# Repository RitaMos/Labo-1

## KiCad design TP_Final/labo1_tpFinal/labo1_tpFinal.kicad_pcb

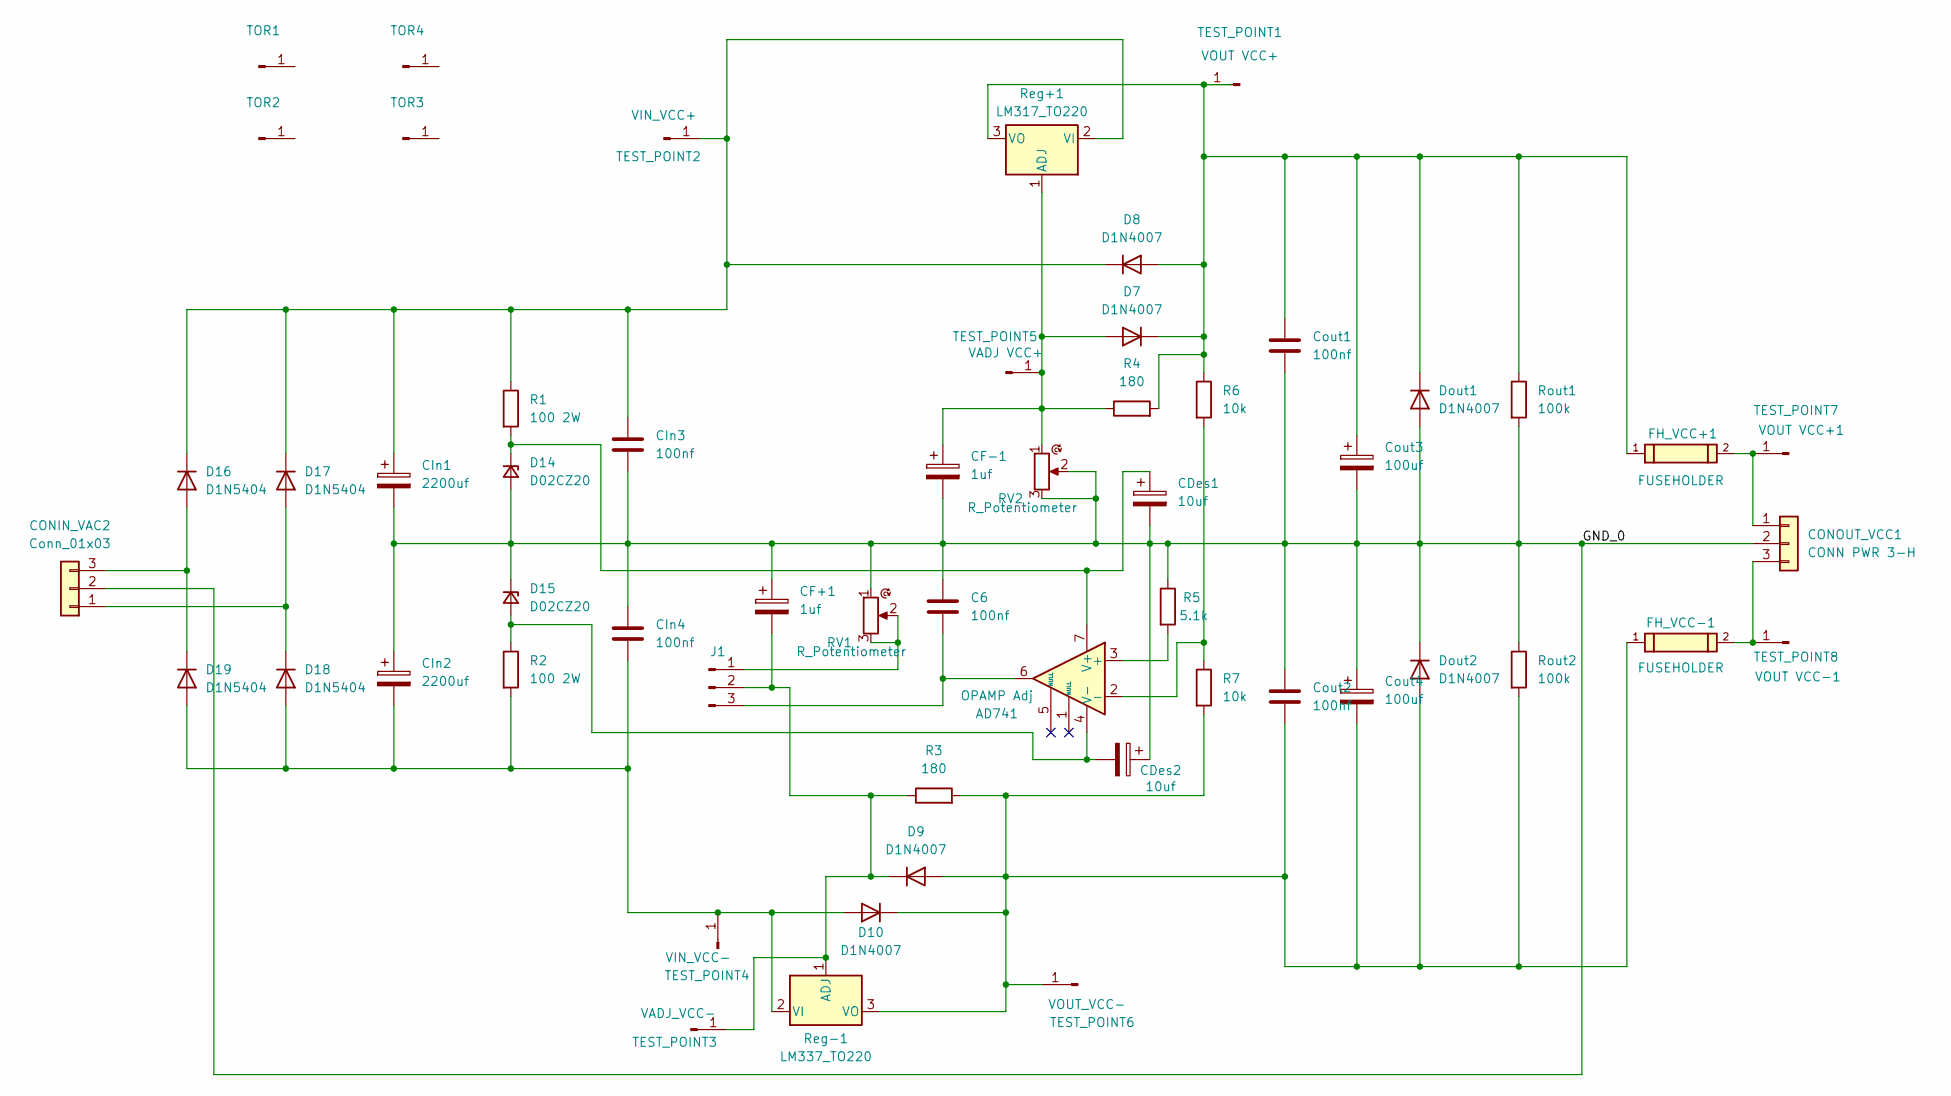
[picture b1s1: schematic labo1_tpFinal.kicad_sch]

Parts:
AD741: OPAMP Adj; N_8_ADI; MPN LM741
C6: 100nf; CAPC2012X140N; MPN C0805Y104K1RACTU
CDes1, CDes2: 10uf; CAPC2012X140N; MPN TLCR106M020RTA
CF+1: 1uf; TACR_AVX; MPN TACR105M025XTA
CF-1: 1uf; TACR_AVX; MPN TACR105M025XTA
CIn1, CIn2: 2200uf; CP_EIA-7260-15_AVX-R; MPN F750G228KRC
CIn3, CIn4: 100nf; CAPC2012X140N; MPN C0805Y104K1RACTU
CONIN_VAC2: Conn_01x03; CONN_A-6373-03A_MOL; MPN 0022232031
CONOUT_VCC1: CONN PWR 3-H; CONN_A-6373-03A_MOL; MPN 0022232031
Cout1, Cout2: 100nf; CAPC2012X140N; MPN C0805Y104K1RACTU
Cout3, Cout4: 100uf; CAPMP7.6X6_3.8N_KEM; MPN T491E107K020AT
D7, D8, D9, D10: D1N4007; P1_DO-41; MPN 1N4007
D14, D15: D02CZ20; SC-59_TOS; MPN 02CZ2.0-X
D16, D17, D18, D19: D1N5404; D_DO-201AD_P15.24mm_Horizontal; MPN 1N5404
Dout1, Dout2: D1N4007; P1_DO-41; MPN 1N4007
FH_VCC+1: FUSEHOLDER; FUSE_01110501Z; MPN 696108003002
FH_VCC-1: FUSEHOLDER; FUSE_01110501Z; MPN 696108003002
J1: Conn_01x03_Pin; WURTH_61300311121; MPN 61300311121
R1, R2: 100 2W; RES_MMP200_YAG-M; MPN MMP200JR-100R
R3, R4: 180; RESC2012X60N; MPN RNCP0805FTD180R
R5: 5.1k; RESC2012X60N; MPN RC0805JR-075K1L
R6, R7: 10k; STA_RMCF0805_STP; MPN RMCF0805FT10K0
RV1, RV2: R_Potentiometer; POT_3296W; MPN 3296W-1-202LF
Reg+1: LM317_TO220; TO254P467X1016X1971-3P; MPN LM317
Reg-1: LM337_TO220; TO-220-3_Vertical; MPN LM337T/NOPB
Rout1, Rout2: 100k; RESC2012X60N; MPN 8-2176765-8
TEST_POINT1: VOUT VCC+; TestPoint_Loop_D2.50mm_Drill1.0mm
TEST_POINT2: VIN_VCC+; TestPoint_Loop_D2.50mm_Drill1.0mm
TEST_POINT3: VADJ_VCC-; TestPoint_Loop_D2.50mm_Drill1.0mm
TEST_POINT4: VIN_VCC-; TestPoint_Loop_D2.50mm_Drill1.0mm
TEST_POINT5: VADJ VCC+; TestPoint_Loop_D2.50mm_Drill1.0mm
TEST_POINT6: VOUT_VCC-; TestPoint_Loop_D2.50mm_Drill1.0mm
TEST_POINT7: VOUT VCC+1; TestPoint_Loop_D2.50mm_Drill1.0mm
TEST_POINT8: VOUT VCC-1; TestPoint_Loop_D2.50mm_Drill1.0mm
TOR1, TOR2, TOR3, TOR4: Conn_01x01_Pin; H212201; MPN H2122-01

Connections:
/GND_0: C6.1, CDes1.2, CDes2.1, CF+1.1, CF-1.2, CIn1.2, CIn2.1, CIn3.2, CIn4.1, CONIN_VAC2.2, CONOUT_VCC1.2, Cout1.2, Cout2.1, Cout3.2, Cout4.1, D14.1 (A), D15.3 (K), Dout1.2 (A), Dout2.1 (K), R5.1, RV1.1, RV2.2, RV2.3, Rout1.2, Rout2.1
unnamed: AD741.3 (+), R5.2
unnamed: AD741.2 (-), R6.2, R7.1
unnamed: AD741.7 (V+), CDes1.1, D14.3 (K), R1.2
unnamed: AD741.4 (V-), CDes2.2, D15.2 (A), R2.1
unnamed: CONIN_VAC2.1, D17.2 (A), D18.1 (K)
unnamed: CONIN_VAC2.3, D16.2 (A), D19.1 (K)
unnamed: CONOUT_VCC1.1, FH_VCC+1.2, TEST_POINT7.1 (Pin_1_1)
unnamed: CONOUT_VCC1.3, FH_VCC-1.2, TEST_POINT8.1 (Pin_1_1)
unnamed: CF-1.1, D7.2 (A), R4.1, RV2.1, Reg+1.1 (ADJ), TEST_POINT5.1 (Pin_1_1)
unnamed: Cout1.1, Cout3.1, D7.1 (K), D8.2 (A), Dout1.1 (K), FH_VCC+1.1, R4.2, R6.1, Reg+1.3 (VO), Rout1.1, TEST_POINT1.1 (Pin_1_1)
unnamed: CF+1.2, D9.1 (K), J1.2, R3.1, Reg-1.1 (ADJ), TEST_POINT3.1 (Pin_1_1)
unnamed: CIn2.2, CIn4.2, D10.2 (A), D18.2 (A), D19.2 (A), R2.2, Reg-1.2 (VI), TEST_POINT4.1 (Pin_1_1)
unnamed: Cout2.2, Cout4.2, D9.2 (A), D10.1 (K), Dout2.2 (A), FH_VCC-1.1, R3.2, R7.2, Reg-1.3 (VO), Rout2.2, TEST_POINT6.1 (Pin_1_1)
unnamed: CIn1.1, CIn3.1, D8.1 (K), D16.1 (K), D17.1 (K), R1.1, Reg+1.2 (VI), TEST_POINT2.1 (Pin_1_1)
unnamed: J1.1, RV1.2, RV1.3
unnamed: AD741.6, C6.2, J1.3

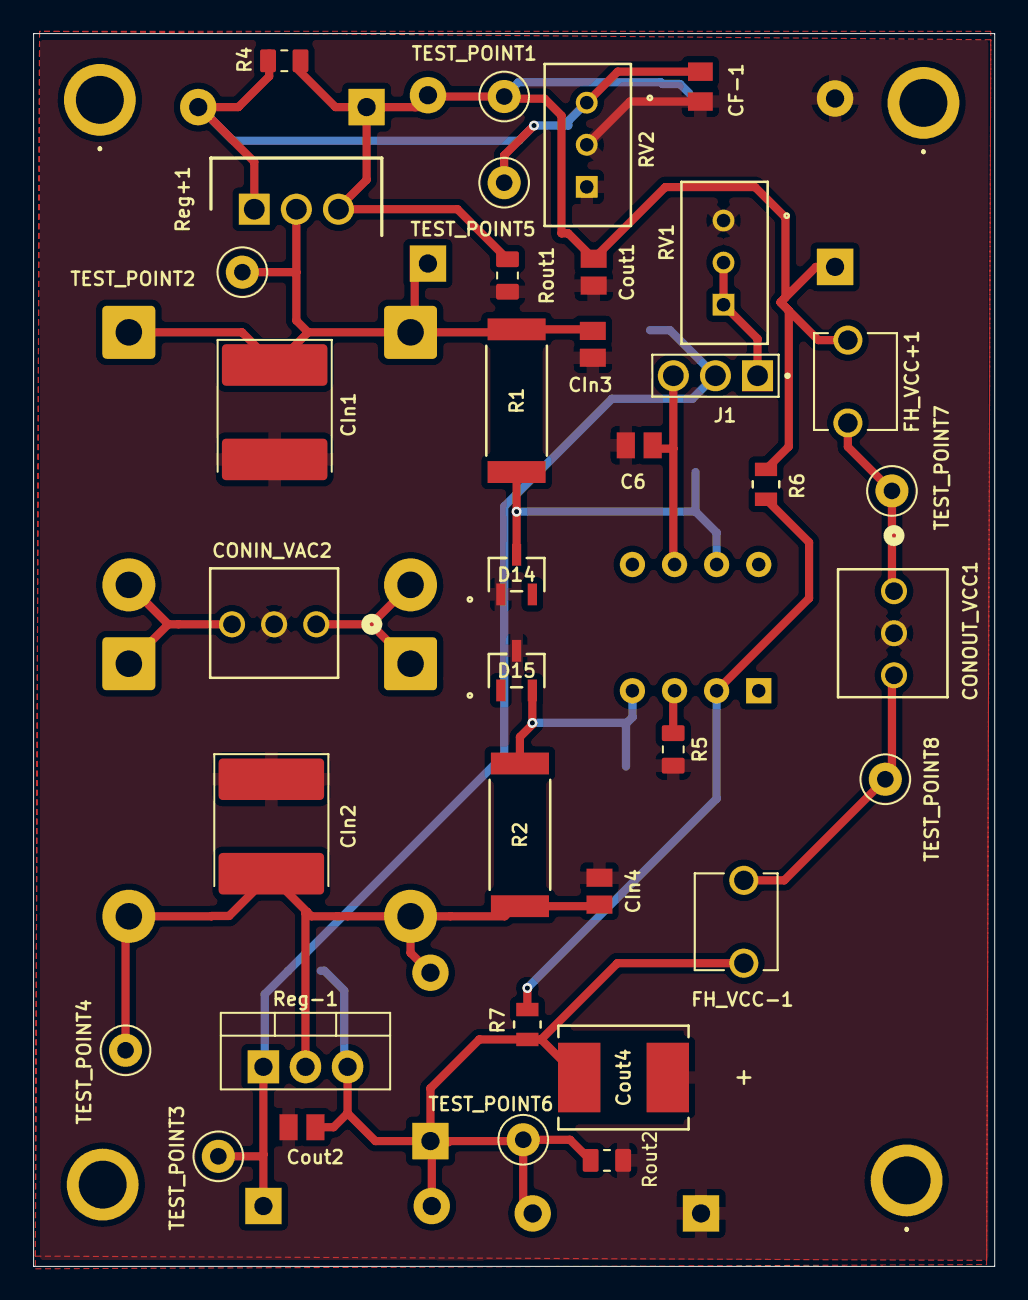
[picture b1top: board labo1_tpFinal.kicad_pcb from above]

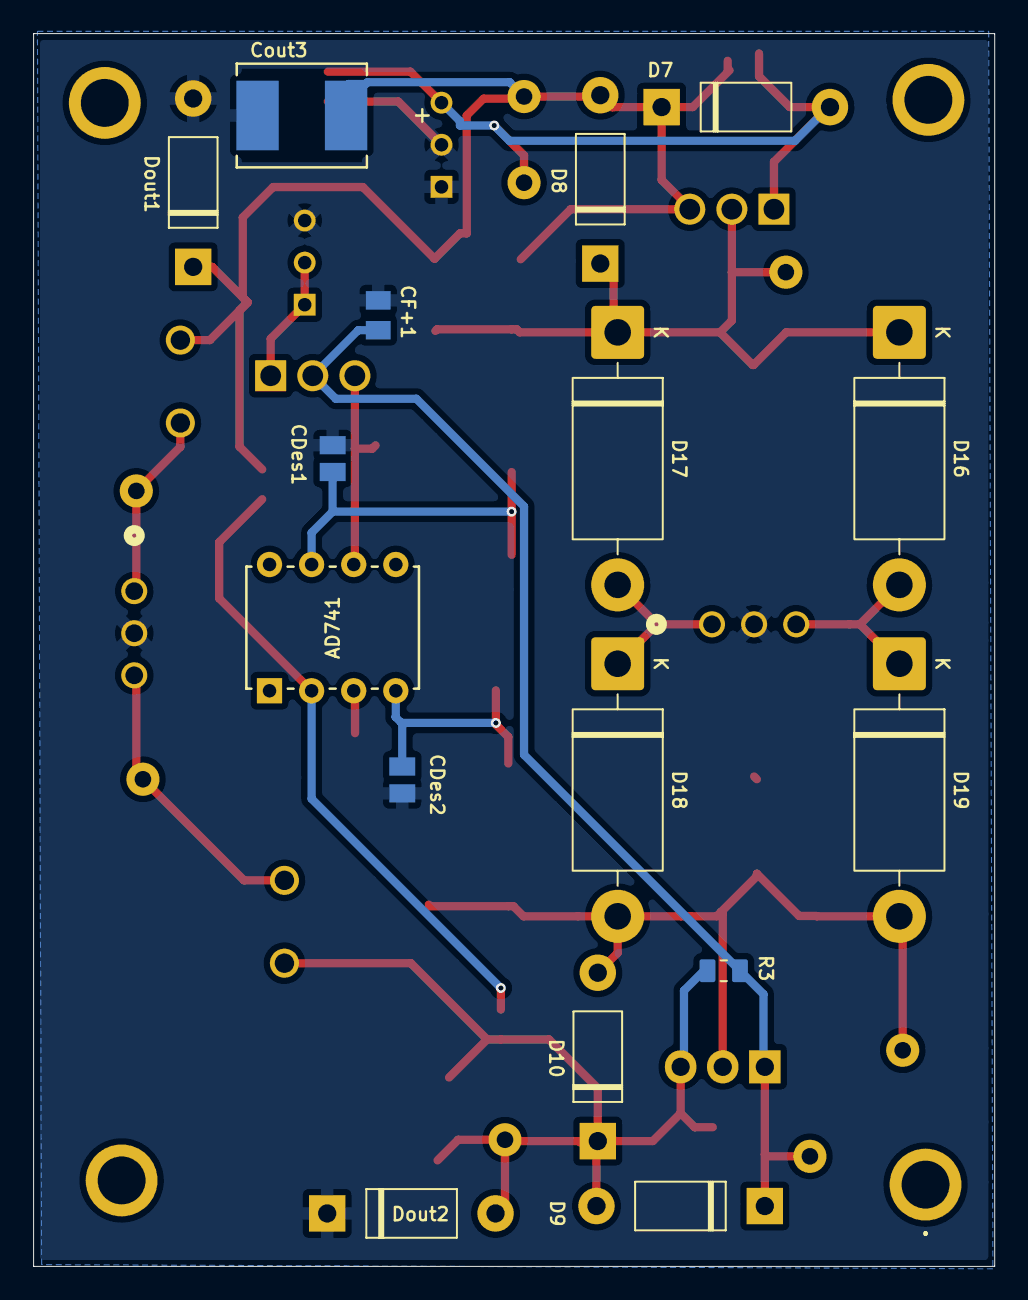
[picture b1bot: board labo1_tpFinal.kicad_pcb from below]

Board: 2 copper layers, 58.0 x 74.4 mm, 56 parts (17 on the bottom side), 17 nets.

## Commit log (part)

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2026-03-21 Añado base
2026-03-24 Meti 2 librerias al preambulo, 1 para graficos de Bode y otra para tablas d:
2026-03-24 termine objetivos, ahora insturemntos y equipos y finalmente introduccion teorica
2026-03-24 Me voy a tomar un ferno y ver un cap de anime. Falta corregir el circuito de tikz y mas marco teorico. Vuelvo en 30/40min
2026-03-24 Ahi termine los bode, circuitos y ecuaciones absicas de la teoria RC. Ahora arranco con el osciloscopio y puntas
2026-03-24 falta las figuras del modelo equivalente de las puntas X1 y X10
2026-03-24 Enhance practical section with analysis and results
    Added detailed analysis and results for practical section of the report, including frequency cutoff calculations, phase angle measurements, frequency response table, and Bode diagram. Included graphs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
2026-03-24 terminado el item a teorico del 2
2026-03-25 pasaaltos pase practica sin terminar
    falta lo de la señal triangular y algunas fotos
2026-03-25 agrego iagenes triangular
2026-03-25 fotos que faltaban parte 2 practica
2026-03-28 terminadas parte 2 practica y parte 3 completa
2026-03-28 parte teorica 1
2026-03-28 por las dudas
2026-03-28 bode nuevo
2026-03-29 achiqué y terminé parte práctica de pasabajos
2026-03-31 Casi termino mi parte, ma;ana la liquido y hago el resto
2026-03-31 1,2,3 terminados, estoy en el 4 y 5 escribiendolos
2026-03-31 reducción de hojas
2026-04-01 reduje los margenes y achique todo lo que pude las imagenes
2026-04-01 Informe terminado falta resumirlo
2026-04-01 version final
2026-04-01 buenoooooo
2026-04-18 primer avance
2026-04-19 graficos
2026-04-24 añado mayoría de pasabajos
2026-04-25 modular
2026-04-25 parte 3 sin terminar
2026-04-25 Ya redacte la parte 6, me falta hacer la transferencia del 5 y pegar las imagenes del 6
2026-04-25 Coloque imagenes del Q y hice el 4.c falta colcoar el grafico del circuito en pasabajos. Puedo reducir 1 hoja del ejercicio 6 si llega a hacer falta. Del 4.c no se si la respuesta al escalon es neces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
2026-04-30 3 terminado, 4.e avanzado (falta parte teorica y comparar)
2026-05-13 parte de 4 mia ya está.
2026-05-13 parte 5 y acomode algunas tablas
2026-05-17 Hice objetivos y el calculo de las corrientes maximas del inductor d:
2026-05-18 Mande cosas al apendice y estructure un poco mejor el informe
2026-05-18 Casi que terminamos TP2
2026-05-19 Añadí el inciso c
2026-05-19 cosas
2026-05-19 ejercicio f
2026-05-19 el que me toca lo del indcutor en tp3 lo hago pija
2026-05-20 C'est fini
2026-05-20 correcciones tp2 listas
2026-05-20 correciones tp3 listas
2026-05-20 entra todo pero esta mal lod elas tablas
2026-06-10 arranque informe TP4
2026-06-11 terminado, falta resumir media carilla
2026-06-11 mayor optimizacion de espacio, ya casi lo logro (aaaaaah)
2026-06-11 ya casi logro resumir suficiente, apendice terminado
2026-06-16 agrego un poco de lo de TP5, tope de 6 hojas
2026-06-19 CAMBIO UN POCO TP5
2026-06-20 parte 5 tp6
2026-06-21 más forma Tp5
2026-06-23 pregunta 2 completa
2026-06-25 Se actualiza sección de puente C serie
2026-06-26 tp analizador espectro finished
2026-06-27 listo wien
